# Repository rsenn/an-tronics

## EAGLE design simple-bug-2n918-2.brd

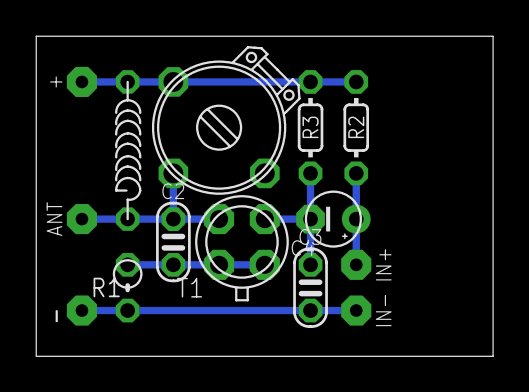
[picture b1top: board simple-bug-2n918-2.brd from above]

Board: 2 copper layers, 25.4 x 17.8 mm, 14 parts (0 on the bottom side), 6 nets.

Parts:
+: SPAD
ANT: ANT; SPAD
C1: 1.6 - 15pF; TRIM-2222-808
C2: 4.7pF; C025-020X036
C3: 1nF; C025-020X036
C4: 1uF; E2,5-3
IN+: SPAD
IN-: SPAD
L1: 1uH; L-02/7
R1: 2.2; 0202V
R2: 22k; 0202/5
R3: 47k; 0202/5
T1: 2N918; TO-72
̶̶: SPAD

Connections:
+UB: +.1, C1.3, L1.1, R2.2, R3.2
GND: C3.2, IN-.1, R1.1, ̶̶.1
IN+: C4.+, IN+.1, R2.1
unnamed: ANT.1, C1.2, C2.1, L1.2, T1.3
unnamed: C2.2, R1.2, T1.1
unnamed: C3.1, C4.-, R3.1, T1.2

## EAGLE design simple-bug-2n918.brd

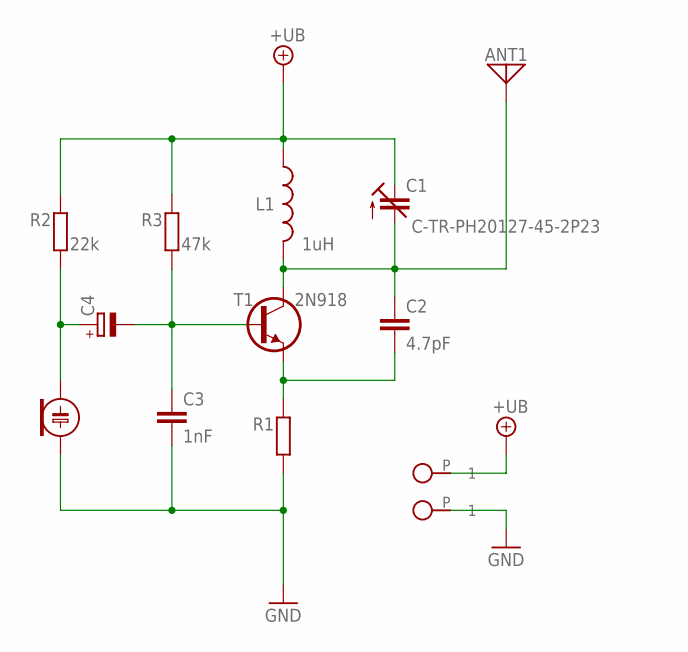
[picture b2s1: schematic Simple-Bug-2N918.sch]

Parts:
+: SPAD
ANT1: ANT; SPAD
C1: C-TR-PH20127-45-2P23; TRIM808-45
C2: 4.7pF; C025-020X036
C3: 1nF; C025-020X036
C4: CPOLE2,5-3; E2,5-3
ECM: ECM-5
L1: 1uH; L-04/7
R1: R0202V; 0202V
R2: 22k; 0202/5
R3: 47k; 0202/5
T1: 2N918; TO-72-A45
̶̶: SPAD

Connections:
+UB: +.P, C1.3 (E), L1.1, R2.2, R3.2
GND: C3.2, ECM.1 (+), R1.1, ̶̶.P
unnamed: ANT1.P, C1.2 (A), C2.1, L1.2, T1.3 (C)
unnamed: C2.2, R1.2, T1.1 (E)
unnamed: C3.1, C4.-, R3.1, T1.2 (B)
unnamed: C4.+, ECM.2 (-), R2.1

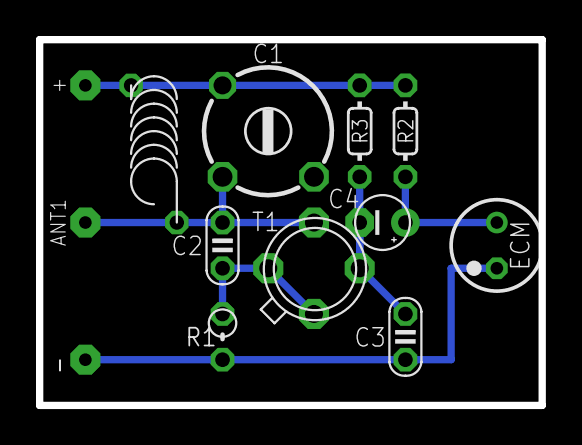
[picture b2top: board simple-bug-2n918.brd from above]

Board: 2 copper layers, 27.9 x 20.3 mm, 13 parts (0 on the bottom side), 6 nets.

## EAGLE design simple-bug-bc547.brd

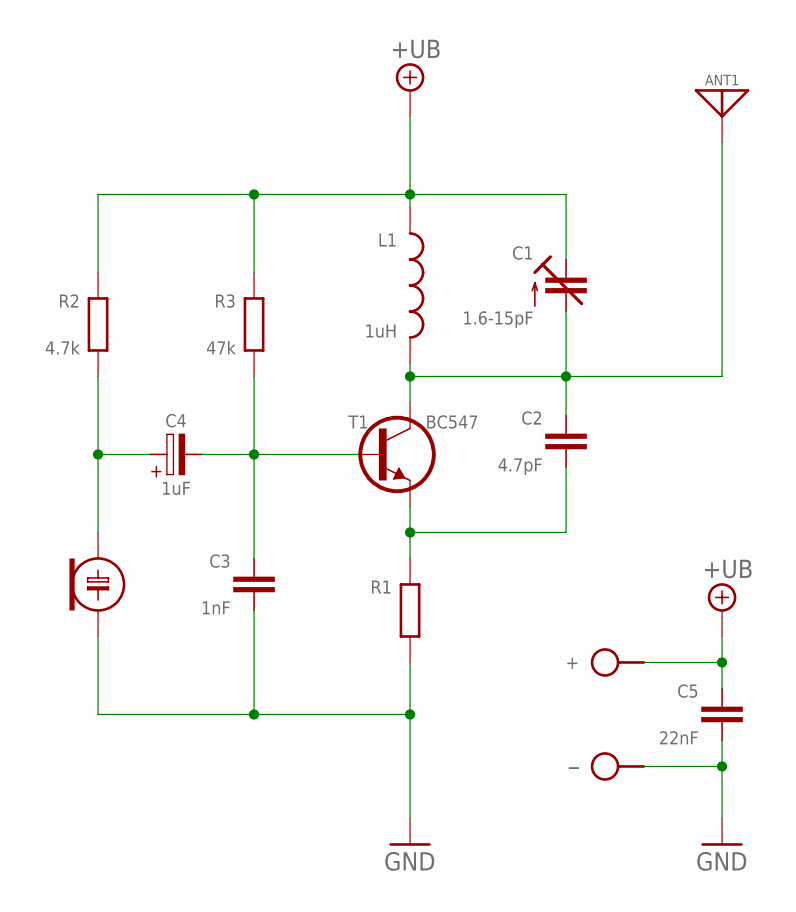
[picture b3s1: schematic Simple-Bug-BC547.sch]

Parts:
+: SPAD
ANT1: ANT; SPAD
C1: 1.6-15pF; TRIM-2222-808
C2: 4.7pF; C050-020X036
C3: 1nF; C050-020X036/V
C4: 1uF; E2,5-3
C5: 22nF; C050-020X036
ECM: ECM-4
L1: 1uH; L-04/7V
R1: R0202/5; 0202/5
R2: 4.7k; 0202/5
R3: 47k; 0202/5
T1: BC547; TO92-CBE-A
̶̶: SPAD

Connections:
+UB: +.1, C1.1 (E), C1.3 (E), C5.1, L1.1, R2.2, R3.2
GND: C3.2, C5.2, ECM.2 (-), R1.1, ̶̶.1
unnamed: ANT1.1, C1.2 (A), C2.1, L1.2, T1.C
unnamed: C2.2, R1.2, T1.E
unnamed: C3.1, C4.-, R3.1, T1.B
unnamed: C4.+, ECM.1 (+), R2.1

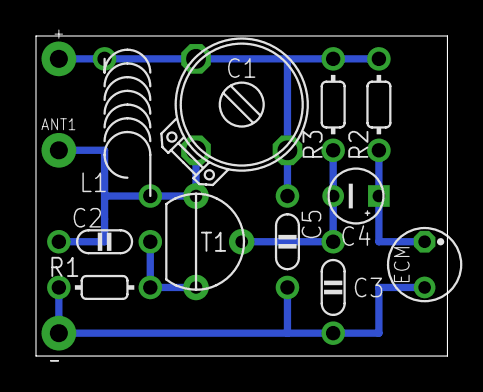
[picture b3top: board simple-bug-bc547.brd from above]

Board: 2 copper layers, 22.9 x 17.8 mm, 14 parts (0 on the bottom side), 6 nets.

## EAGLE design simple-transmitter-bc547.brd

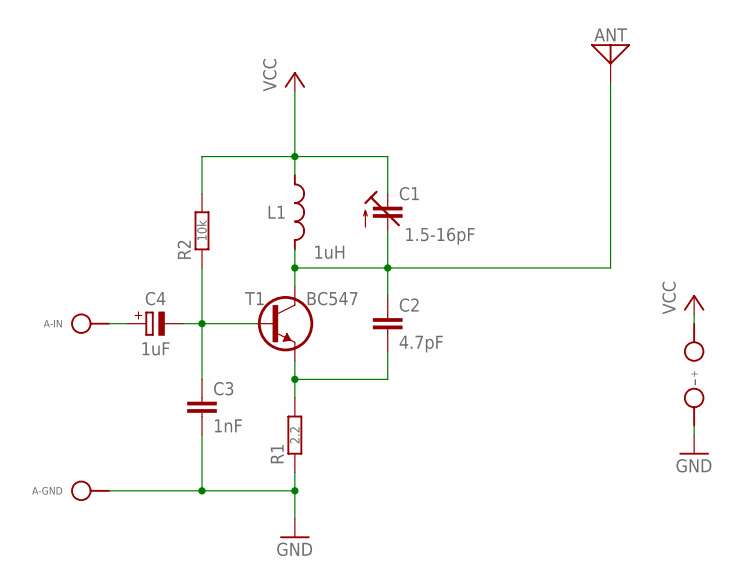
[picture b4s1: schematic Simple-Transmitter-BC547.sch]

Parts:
+: SPAD
A-GND: SPAD
A-IN: SPAD
ANT: ANT; SPAD
C1: 1.5-16pF; TRIM808-45
C2: 4.7pF; C050-020X036-M
C3: 1nF; C050-020X036
C4: 1uF; E2,5-3
L1: 1uH; L-04/7
R1: 2.2; 0202V
R2: 10k; 0202/5-V
T1: BC547; TO92-CBE
̶̶: SPAD

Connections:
+UB: +.1, C1.3 (A), L1.1, R2.2; also elsewhere on the board
AIN: A-IN.1, C4.+
GND: A-GND.1, C3.2, R1.1, ̶̶.1
unnamed: ANT.1, C1.2 (E), C2.1, L1.2, T1.C
unnamed: C2.2, R1.2, T1.E
unnamed 5: C3.1, C4.-, R2.1, T1.B; also elsewhere on the board

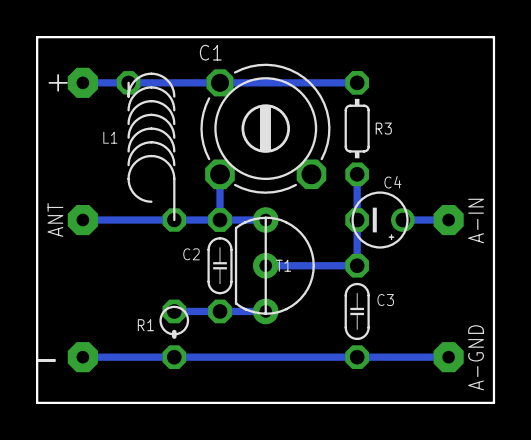
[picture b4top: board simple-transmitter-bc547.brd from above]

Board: 2 copper layers, 25.4 x 20.3 mm, 13 parts (0 on the bottom side), 6 nets.

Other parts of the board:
R3: 47k; 0202/5

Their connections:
+UB: R3.2; also elsewhere on the board
unnamed 5: R3.1; also elsewhere on the board

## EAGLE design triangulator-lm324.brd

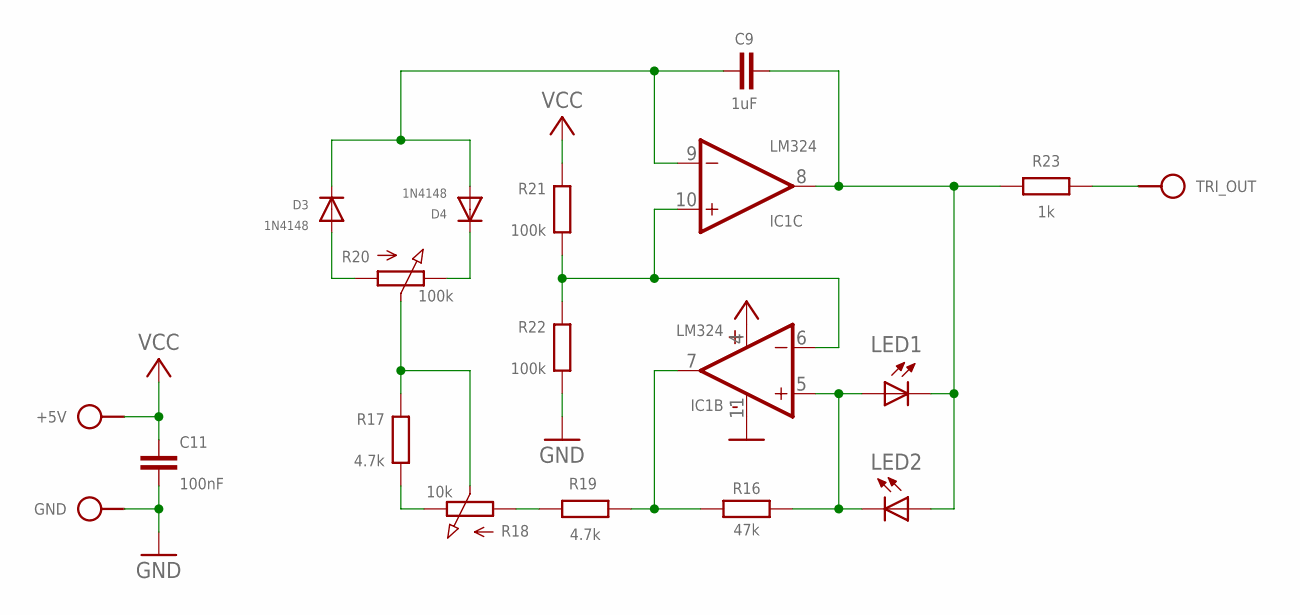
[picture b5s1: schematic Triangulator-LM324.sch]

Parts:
+5V: VCC; SPAD
C9: 1uF; C050-024X044/V
C11: 100nF; C050-020X036
D3, D4: 1N4148; DO34-7V
GND: GND; SPAD
IC1: LM324; DIL14
LED1, LED2: LED3MM
R16: 47k; 0202/7-V
R17: 4.7k; 0202/7
R18: 10k; POT
R19: 4.7k; 0202/7-V
R20: 100k; POT
R21, R22: 100k; 0202/7-V
R23: 1k; 0202/7-V
TRI_OUT: TRIANGLE; SPAD

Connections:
GND: C11.2, GND.1, IC1.11 (V-), R22.1
unnamed: IC1.7 (OUT), R16.2, R19.1
unnamed: IC1.5 (+IN), LED1.A, LED2.K (C), R16.1
unnamed: D3.A, R20.1 (A)
unnamed: D4.C, R20.3 (E)
unnamed: R17.2, R18.2 (S), R20.2 (S)
unnamed: R17.1, R18.3 (E)
unnamed: C9.1, D3.C, D4.A, IC1.9 (-IN)
unnamed: R18.1 (A), R19.2
unnamed: C9.2, IC1.8 (OUT), LED1.K (C), LED2.A, R23.2
unnamed: R23.1, TRI_OUT.1
unnamed: IC1.6 (-IN), IC1.10 (+IN), R21.1, R22.2
VCC: +5V.1, C11.1, IC1.4 (V+), R21.2

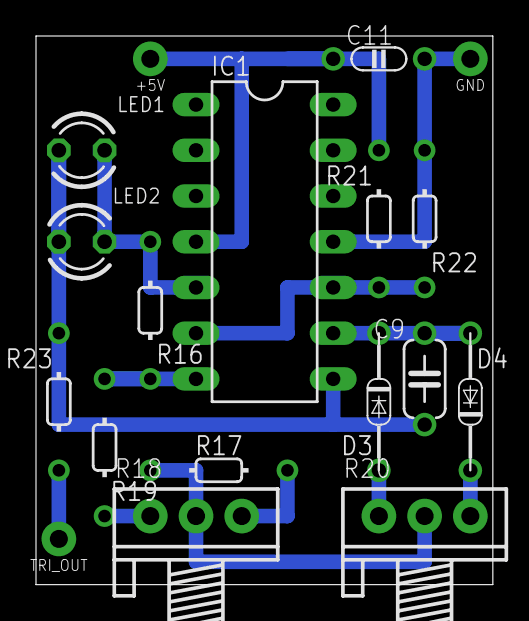
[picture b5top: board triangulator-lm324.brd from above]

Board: 2 copper layers, 25.4 x 30.5 mm, 18 parts (0 on the bottom side), 13 nets.
